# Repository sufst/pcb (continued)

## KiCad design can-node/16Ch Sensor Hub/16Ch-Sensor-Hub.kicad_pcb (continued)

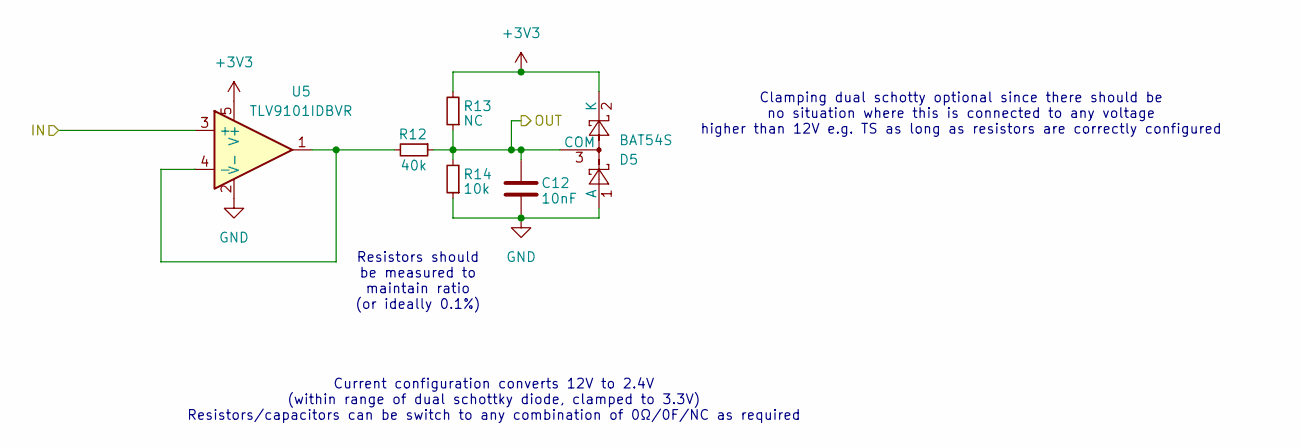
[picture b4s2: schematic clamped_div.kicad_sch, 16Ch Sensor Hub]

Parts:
C12: 10nF; C_0603_1608Metric_Pad1.08x0.95mm_HandSolder
D5: BAT54S; SOT-23
R12: 40k; R_0603_1608Metric_Pad0.98x0.95mm_HandSolder; Manufacturer_Part_Number CRCW080540K0FKEA; Mouser Part Number 71-CRCW080540K0FKEA
R13: NC; R_0603_1608Metric_Pad0.98x0.95mm_HandSolder; Manufacturer_Part_Number CRGH0805F12R; Mouser Part Number 279-CRGH0805F12R
R14: 10k; R_0603_1608Metric_Pad0.98x0.95mm_HandSolder; Manufacturer_Part_Number CRGH0805F12R; Mouser Part Number 279-CRGH0805F12R
U5: TLV9101IDBVR; SOT-23-5_HandSoldering

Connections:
+3V3: D5.2 (K), R13.2, U5.5 (V+); also elsewhere on the board
/ADC_L_4: C12.1, D5.3 (COM), R12.1, R13.1, R14.2; also elsewhere on the board
/ClampedDivider6/IN: U5.3 (+); also elsewhere on the board
GND: C12.2, D5.1 (A), R14.1, U5.2 (V-); also elsewhere on the board
unnamed: R12.2, U5.1, U5.4 (-)

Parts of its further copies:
C11, C13, C14, C15, C16, C17, C18, C19, C20, C21, C22, C23, C24, C25, C26: 10nF; C_0603_1608Metric_Pad1.08x0.95mm_HandSolder
D4, D6, D7, D8, D9, D10, D11, D12, D13, D14, D15, D16, D17, D18, D19: BAT54S; SOT-23
R9, R15, R18, R21, R24, R27, R30, R33, R36, R39, R42, R45, R48, R51, R54: 40k; R_0603_1608Metric_Pad0.98x0.95mm_HandSolder; Manufacturer_Part_Number CRCW080540K0FKEA; Mouser Part Number 71-CRCW080540K0FKEA
R10, R16, R19, R22, R25, R28, R31, R34, R37, R40, R43, R46, R49, R52, R55: NC; R_0603_1608Metric_Pad0.98x0.95mm_HandSolder; Manufacturer_Part_Number CRGH0805F12R; Mouser Part Number 279-CRGH0805F12R
R11, R17, R20, R23, R26, R29, R32, R35, R38, R41, R44, R47, R50, R53, R56: 10k; R_0603_1608Metric_Pad0.98x0.95mm_HandSolder; Manufacturer_Part_Number CRGH0805F12R; Mouser Part Number 279-CRGH0805F12R
U4, U6, U7, U8, U9, U10, U11, U12, U13, U14, U15, U16, U17, U18, U19: TLV9101IDBVR; SOT-23-5_HandSoldering

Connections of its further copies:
+3V3: D4.2 (K), D6.2 (K), D7.2 (K), D8.2 (K), D9.2 (K), D10.2 (K), D11.2 (K), D12.2 (K), D13.2 (K), D14.2 (K), D15.2 (K), D16.2 (K), D17.2 (K), D18.2 (K), D19.2 (K), R10.2, R16.2, R19.2, R22.2, R25.2, R28.2, R31.2, R34.2, R37.2, R40.2, R43.2, R46.2, R49.2, R52.2, R55.2, U4.5 (V+), U6.5 (V+), U7.5 (V+), U8.5 (V+), U9.5 (V+), U10.5 (V+), U11.5 (V+), U12.5 (V+), U13.5 (V+), U14.5 (V+), U15.5 (V+), U16.5 (V+), U17.5 (V+), U18.5 (V+), U19.5 (V+); also elsewhere on the board
/ADC_L_1: C15.1, D8.3 (COM), R21.1, R22.1, R23.2; also elsewhere on the board
/ADC_L_2: C16.1, D9.3 (COM), R24.1, R25.1, R26.2; also elsewhere on the board
/ADC_L_3: C11.1, D4.3 (COM), R9.1, R10.1, R11.2; also elsewhere on the board
/ADC_L_5: C17.1, D10.3 (COM), R27.1, R28.1, R29.2; also elsewhere on the board
/ADC_L_6: C18.1, D11.3 (COM), R30.1, R31.1, R32.2; also elsewhere on the board
/ADC_L_7: C13.1, D6.3 (COM), R15.1, R16.1, R17.2; also elsewhere on the board
/ADC_L_8: C14.1, D7.3 (COM), R18.1, R19.1, R20.2; also elsewhere on the board
/ADC_R_1: C23.1, D16.3 (COM), R45.1, R46.1, R47.2; also elsewhere on the board
/ADC_R_2: C24.1, D17.3 (COM), R48.1, R49.1, R50.2; also elsewhere on the board
/ADC_R_3: C19.1, D12.3 (COM), R33.1, R34.1, R35.2; also elsewhere on the board
/ADC_R_4: C20.1, D13.3 (COM), R36.1, R37.1, R38.2; also elsewhere on the board
/ADC_R_5: C25.1, D18.3 (COM), R51.1, R52.1, R53.2; also elsewhere on the board
/ADC_R_6: C26.1, D19.3 (COM), R54.1, R55.1, R56.2; also elsewhere on the board
/ADC_R_7: C21.1, D14.3 (COM), R39.1, R40.1, R41.2; also elsewhere on the board
/ADC_R_8: C22.1, D15.3 (COM), R42.1, R43.1, R44.2; also elsewhere on the board
/ClampedDivider1/IN: U8.3 (+); also elsewhere on the board
/ClampedDivider2/IN: U9.3 (+); also elsewhere on the board
/ClampedDivider3/IN: U10.3 (+); also elsewhere on the board
/ClampedDivider4/IN: U11.3 (+); also elsewhere on the board
/ClampedDivider5/IN: U4.3 (+); also elsewhere on the board
/ClampedDivider7/IN: U6.3 (+); also elsewhere on the board
/ClampedDivider8/IN: U7.3 (+); also elsewhere on the board
/ClampedDivider9/IN: U16.3 (+); also elsewhere on the board
/ClampedDivider10/IN: U17.3 (+); also elsewhere on the board
/ClampedDivider11/IN: U18.3 (+); also elsewhere on the board
/ClampedDivider12/IN: U19.3 (+); also elsewhere on the board
/ClampedDivider13/IN: U12.3 (+); also elsewhere on the board
/ClampedDivider14/IN: U13.3 (+); also elsewhere on the board
/ClampedDivider15/IN: U14.3 (+); also elsewhere on the board
/ClampedDivider16/IN: U15.3 (+); also elsewhere on the board
GND: C11.2, C13.2, C14.2, C15.2, C16.2, C17.2, C18.2, C19.2, C20.2, C21.2, C22.2, C23.2, C24.2, C25.2, C26.2, D4.1 (A), D6.1 (A), D7.1 (A), D8.1 (A), D9.1 (A), D10.1 (A), D11.1 (A), D12.1 (A), D13.1 (A), D14.1 (A), D15.1 (A), D16.1 (A), D17.1 (A), D18.1 (A), D19.1 (A), R11.1, R17.1, R20.1, R23.1, R26.1, R29.1, R32.1, R35.1, R38.1, R41.1, R44.1, R47.1, R50.1, R53.1, R56.1, U4.2 (V-), U6.2 (V-), U7.2 (V-), U8.2 (V-), U9.2 (V-), U10.2 (V-), U11.2 (V-), U12.2 (V-), U13.2 (V-), U14.2 (V-), U15.2 (V-), U16.2 (V-), U17.2 (V-), U18.2 (V-), U19.2 (V-); also elsewhere on the board
unnamed: R9.2, U4.1, U4.4 (-)
unnamed: R15.2, U6.1, U6.4 (-)
unnamed: R18.2, U7.1, U7.4 (-)
unnamed: R21.2, U8.1, U8.4 (-)
unnamed: R24.2, U9.1, U9.4 (-)
unnamed: R27.2, U10.1, U10.4 (-)
unnamed: R30.2, U11.1, U11.4 (-)
unnamed: R33.2, U12.1, U12.4 (-)
unnamed: R36.2, U13.1, U13.4 (-)
unnamed: R39.2, U14.1, U14.4 (-)
unnamed: R42.2, U15.1, U15.4 (-)
unnamed: R45.2, U16.1, U16.4 (-)
unnamed: R48.2, U17.1, U17.4 (-)
unnamed: R51.2, U18.1, U18.4 (-)
unnamed: R54.2, U19.1, U19.4 (-)

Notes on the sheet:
Current configuration converts 12V to 2.4V (within range of dual schottky diode, clamped to 3.3V) Resistors/capacitors can be switch to any combination of 0Ω/0F/NC as required
Clamping dual schotty optional since there should be no situation where this is connected to any voltage higher than 12V e.g. TS as long as resistors are correctly configured
Resistors should be measured to maintain ratio (or ideally 0.1%)

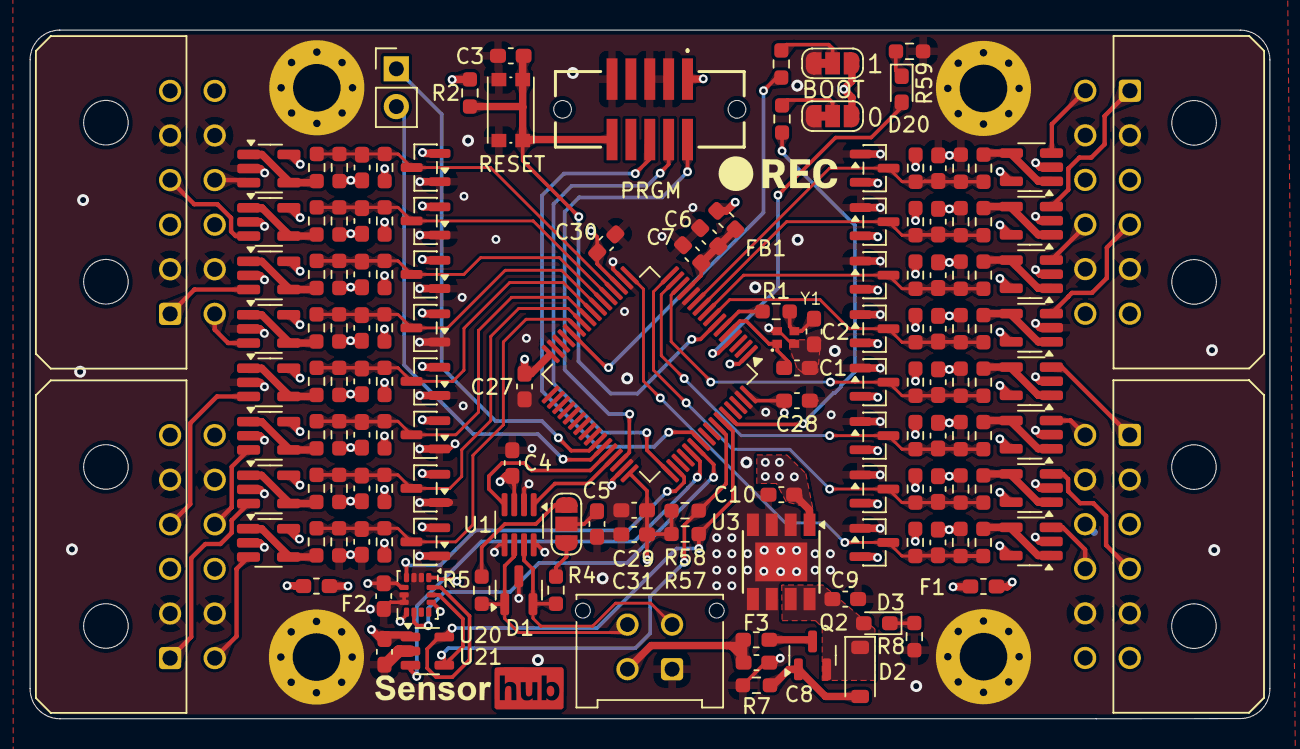
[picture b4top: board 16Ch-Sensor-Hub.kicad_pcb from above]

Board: 4 copper layers, 83.4 x 46.3 mm, 154 parts (0 on the bottom side), 85 nets.
